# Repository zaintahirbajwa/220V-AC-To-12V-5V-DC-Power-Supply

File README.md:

# 220V AC to 12V/5V DC Power Supply

A PCB-based power supply designed to convert **220V AC mains voltage into 12V and 5V DC outputs** for powering low-voltage electronic circuits.

## Project Overview

This project includes the complete PCB design process, from schematic design and PCB routing to 3D visualization and final assembly.

## Features

* 220V AC input
* 12V DC output
* 5V DC output
* PCB designed using **KiCad**
* Custom PCB layout and routing
* 3D PCB model
* Final assembled power supply
* Suitable for low-voltage electronic circuits

## Repository Contents

```text
.
├── Power Supply/
├── Final Power Supply.png
├── PCB 3D Model.jpeg
├── PCB Routes.jpeg
├── PCB Schematic.jpeg
└── README.md
```

## Project Files

| File                     | Description                    |
| ------------------------ | ------------------------------ |
| `Power Supply/`          | KiCad project and design files |
| `Final Power Supply.png` | Final assembled power supply   |
| `PCB 3D Model.jpeg`      | 3D view of the PCB             |
| `PCB Routes.jpeg`        | PCB routing/layout             |
| `PCB Schematic.jpeg`     | Circuit schematic              |

## Software Used

* **KiCad**
* Schematic Capture
* PCB Layout & Routing
* 3D PCB Visualization

## Applications

The 12V and 5V outputs can be used to power:

* Microcontrollers
* Sensors
* LEDs
* Relays
* Other low-voltage electronic circuits

## Safety

This project works with **220V AC mains voltage**. Proper insulation, isolation, fusing, grounding, and adequate PCB clearance are required. Mains-connected circuits should only be assembled and tested using appropriate electrical safety procedures.

## Author

**Zain Tahir**

**COMSATS University Islamabad**

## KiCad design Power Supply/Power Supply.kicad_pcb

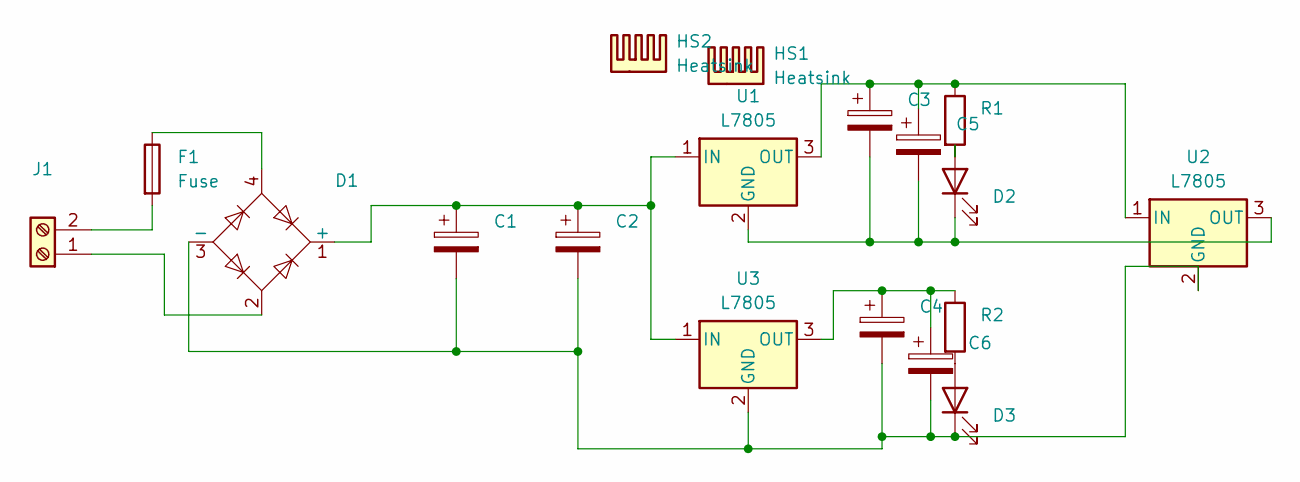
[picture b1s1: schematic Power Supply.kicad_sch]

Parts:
C1: C_Polarized; CP_Radial_D16.0mm_P7.50mm
C2, C3, C4: C_Polarized; C_Disc_D3.8mm_W2.6mm_P2.50mm
C5: C_Polarized; C_Radial_D10.0mm_H12.5mm_P5.00mm
C6: C_Polarized; C_Radial_D10.0mm_H16.0mm_P5.00mm
D1: W01G; Diode_Bridge_Round_D9.8mm
D2, D3: LED; LED_D5.0mm
F1: Fuse; Fuse_Bourns_MF-RG650
HS1: Heatsink; Heatsink_Stonecold_HS-S02_13.21x9.53mm
HS2: Heatsink; Fuse_0402_1005Metric_Pad0.77x0.64mm_HandSolder
J1: Screw_Terminal_01x02; Fuse_0402_1005Metric_Pad0.77x0.64mm_HandSolder
R1, R2: R; R_Axial_DIN0309_L9.0mm_D3.2mm_P15.24mm_Horizontal
U1, U2, U3: L7805; TO-220-3_Vertical

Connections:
unnamed: C1.1, C2.1, D1.1 (+), U1.1 (IN), U3.1 (IN)
unnamed: C1.2, C2.2, C4.2, C6.2, D1.3 (-), D3.1 (K), U2.2 (GND), U3.2 (GND)
unnamed: D1.4, F1.1
unnamed: D2.2 (A), R1.2
unnamed: C3.2, C5.2, D2.1 (K), U1.2 (GND), U2.3 (OUT)
unnamed: D3.2 (A), R2.2
unnamed: D1.2, J1.1
unnamed: F1.2, J1.2
unnamed: C3.1, C5.1, R1.1, U1.3 (OUT), U2.1 (IN)
unnamed: C4.1, C6.1, R2.1, U3.3 (OUT)

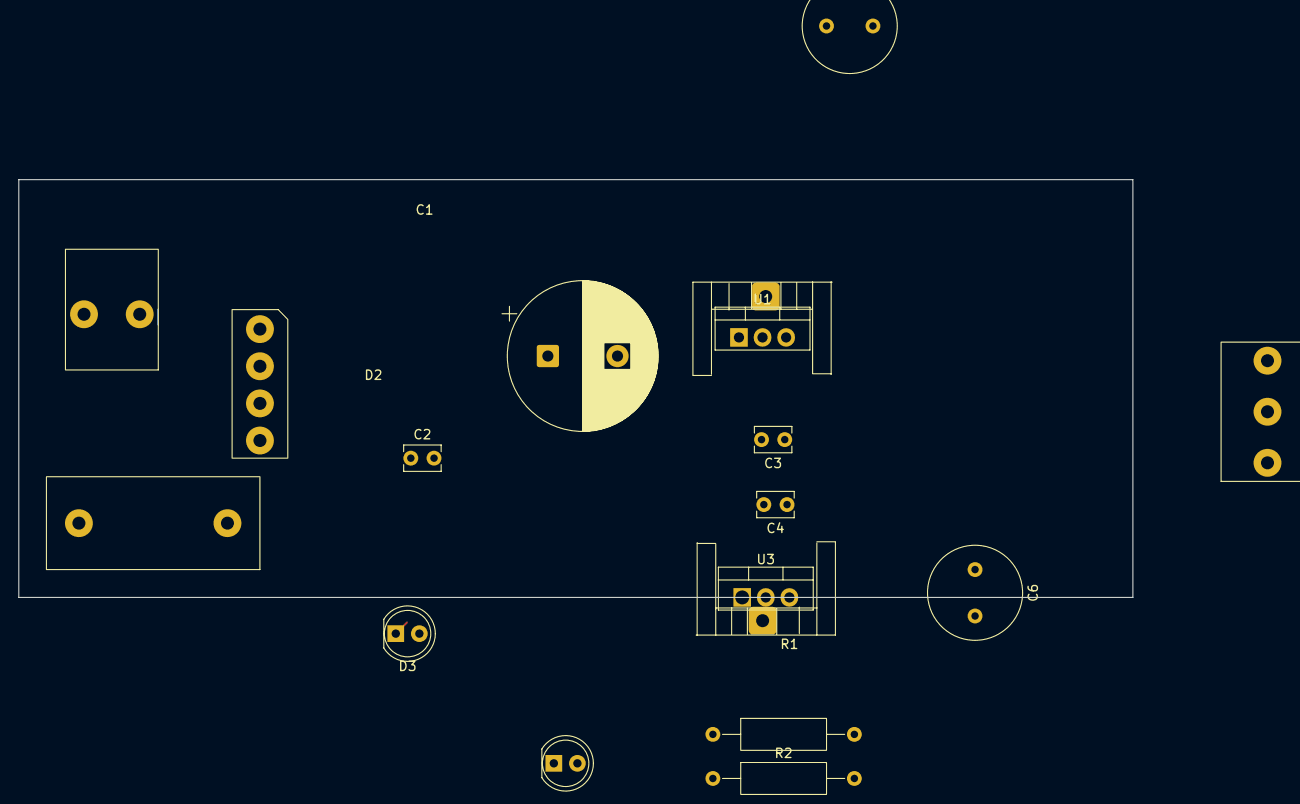
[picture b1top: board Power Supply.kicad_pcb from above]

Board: 2 copper layers, 120.0 x 45.0 mm, 18 parts (0 on the bottom side), 10 nets.
